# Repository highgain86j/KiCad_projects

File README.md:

# KiCad_projects
This repository contains works by the author using KiCad. May contain stuff that are very far from being complete...

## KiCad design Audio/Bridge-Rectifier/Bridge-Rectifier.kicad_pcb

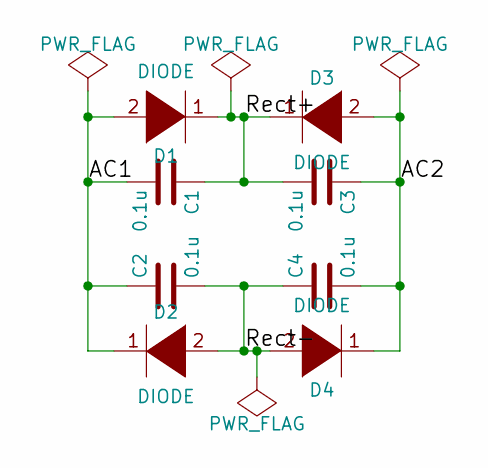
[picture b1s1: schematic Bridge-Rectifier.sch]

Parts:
C1, C2, C3, C4: 0.1u; C_Rect_L13_W6_H12_P10
D1, D2, D3, D4: DIODE; Diode_TO-220_Vertical

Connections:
/AC1: C1.2, C2.1, D1.2 (A), D2.1 (K)
/AC2: C3.1, C4.2, D3.2 (A), D4.1 (K)
/Rect+: C1.1, C3.2, D1.1 (K), D3.1 (K)
/Rect-: C2.2, C4.1, D2.2 (A), D4.2 (A)

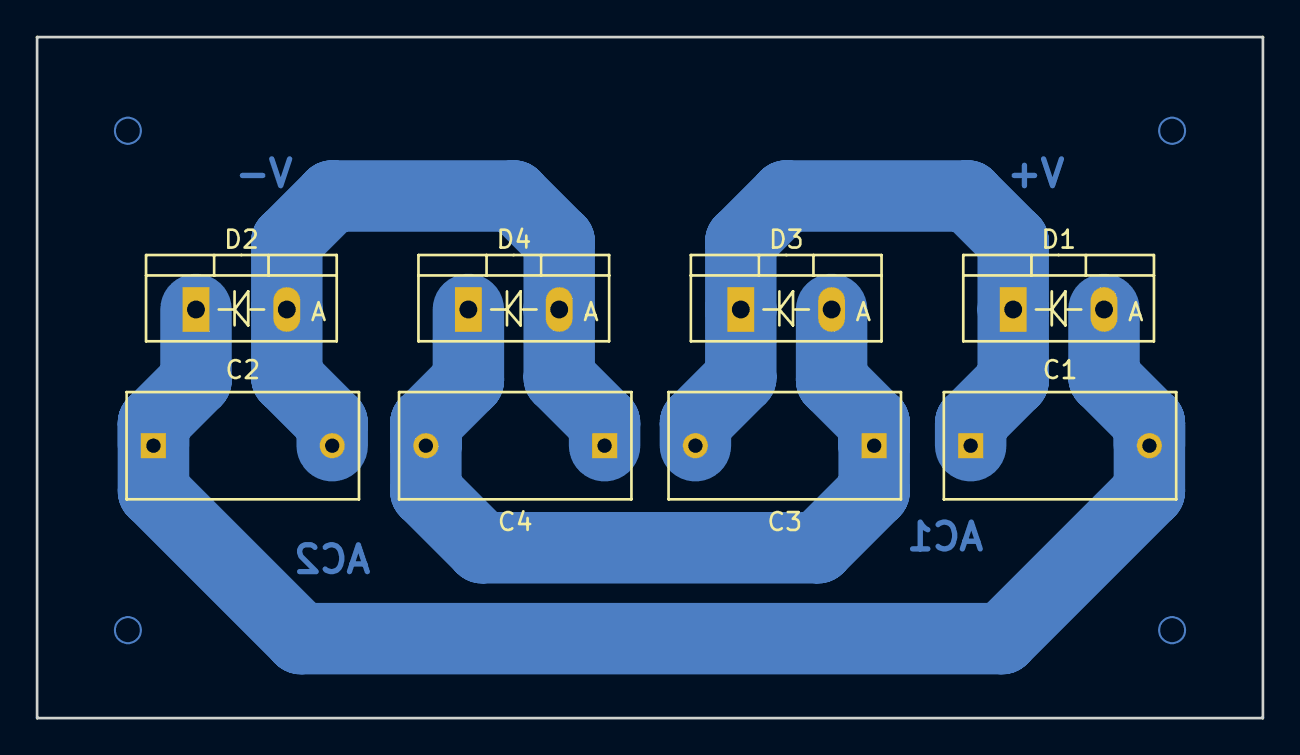
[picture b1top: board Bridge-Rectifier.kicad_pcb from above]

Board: 2 copper layers, 68.6 x 38.1 mm, 8 parts (0 on the bottom side), 4 nets.

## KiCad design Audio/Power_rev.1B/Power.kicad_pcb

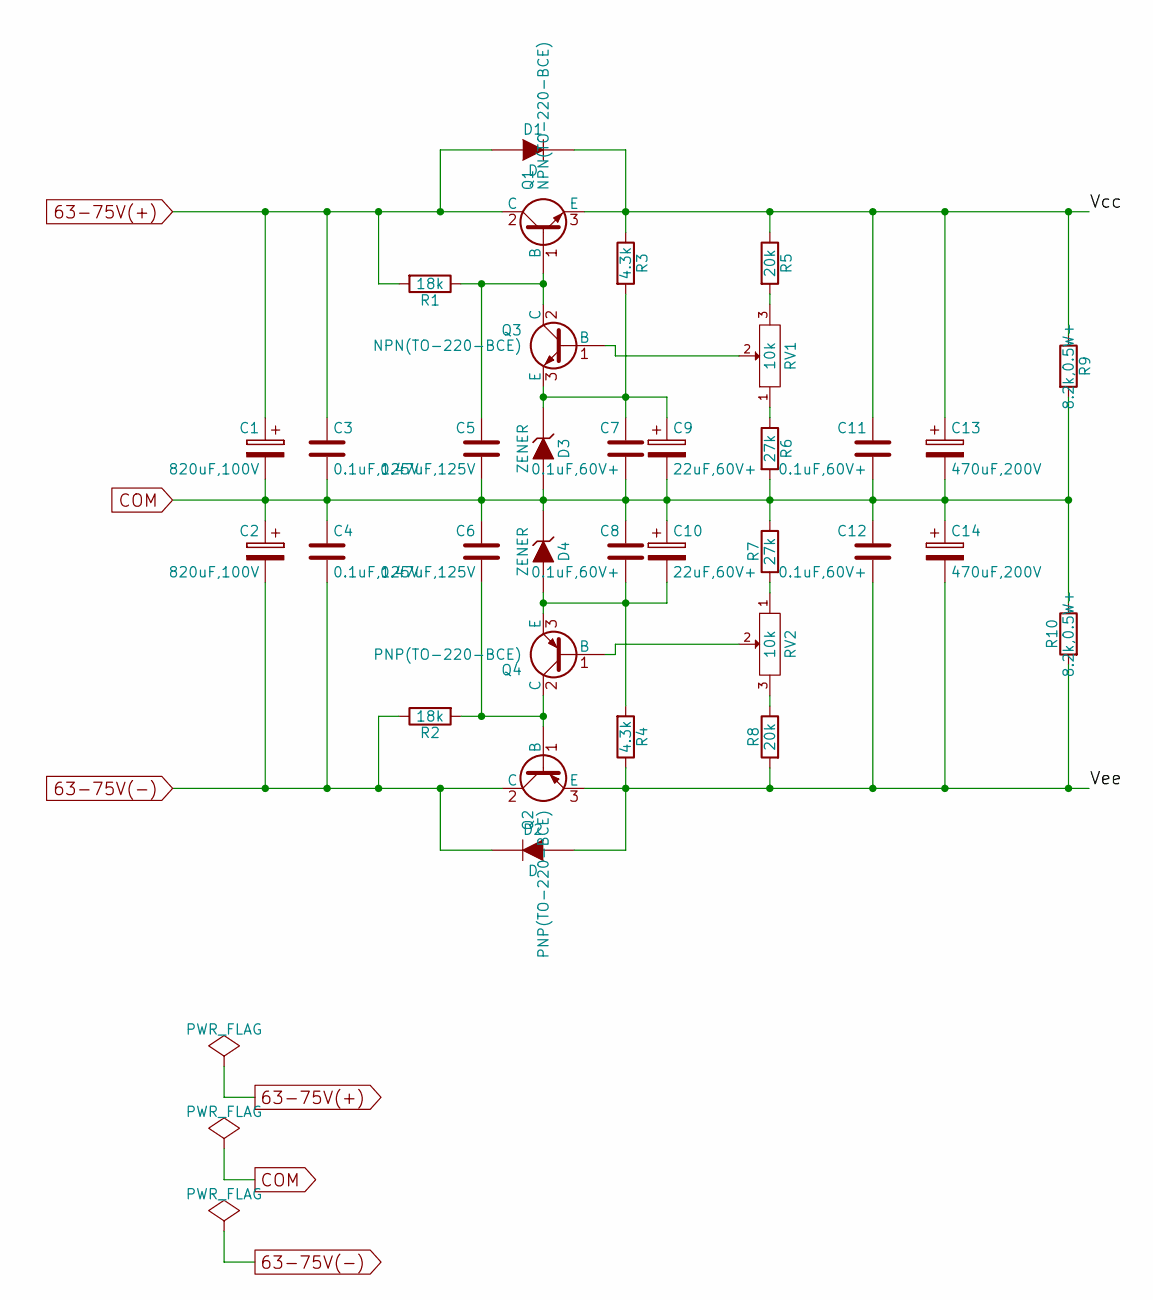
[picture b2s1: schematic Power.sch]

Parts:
C1, C2: 820uF,100V; C_Radial_D18_L36_P7.5
C3, C4: 0.1uF,125V; C_Rect_L18_W6_H12_P15
C5, C6: 0.47uF,125V; C_Rect_L18_W6_H12_P15
C7, C8, C11, C12: 0.1uF,60V+; C_Rect_L18_W6_H12_P15
C9, C10: 22uF,60V+; C_Radial_D10_L20_P5
C13, C14: 470uF,200V; C_Radial_D18_L36_P7.5
D1, D2: D; Diode_DO-35_SOD27_Horizontal_RM10
D3, D4: ZENER; Diode_DO-35_SOD27_Horizontal_RM10
Q1, Q3: NPN(TO-220-BCE); TO-220_Neutral123_Vertical_LargePads
Q2, Q4: PNP(TO-220-BCE); TO-220_Neutral123_Vertical_LargePads
R1, R2: 18k; Resistor_Horizontal_RM10mm
R3, R4: 4.3k; Resistor_Horizontal_RM10mm
R5, R8: 20k; Resistor_Horizontal_RM10mm
R6, R7: 27k; Resistor_Horizontal_RM10mm
R9, R10: 8.2k,0.5W+; Resistor_Horizontal_RM15mm
RV1, RV2: 10k; Potentiometer_Bourns_3296W_3-8Zoll_Inline_ScrewUp

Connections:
63-75V(+): C1.1, C3.1, D1.1 (A), Q1.2 (C), R1.2
63-75V(-): C2.2, C4.2, D2.2 (K), Q2.2 (C), R2.1
/Vcc: C11.1, C13.1, D1.2 (K), Q1.3 (E), R3.1, R5.1, R9.1
/Vee: C12.2, C14.2, D2.1 (A), Q2.3 (E), R4.1, R8.2, R10.2
COM: C1.2, C2.1, C3.2, C4.1, C5.2, C6.1, C7.2, C8.1, C9.2, C10.1, C11.2, C12.1, C13.2, C14.1, D3.2 (A), D4.1 (K), R6.2, R7.1, R9.2, R10.1
unnamed: C5.1, Q1.1 (B), Q3.2 (C), R1.1
unnamed: C6.2, Q2.1 (B), Q4.2 (C), R2.2
unnamed: C7.1, C9.1, D3.1 (K), Q3.3 (E), R3.2
unnamed: C8.2, C10.2, D4.2 (A), Q4.3 (E), R4.2
unnamed: Q3.1 (B), RV1.2
unnamed: Q4.1 (B), RV2.2
unnamed: R5.2, RV1.3
unnamed: R6.1, RV1.1
unnamed: R7.2, RV2.1
unnamed: R8.1, RV2.3

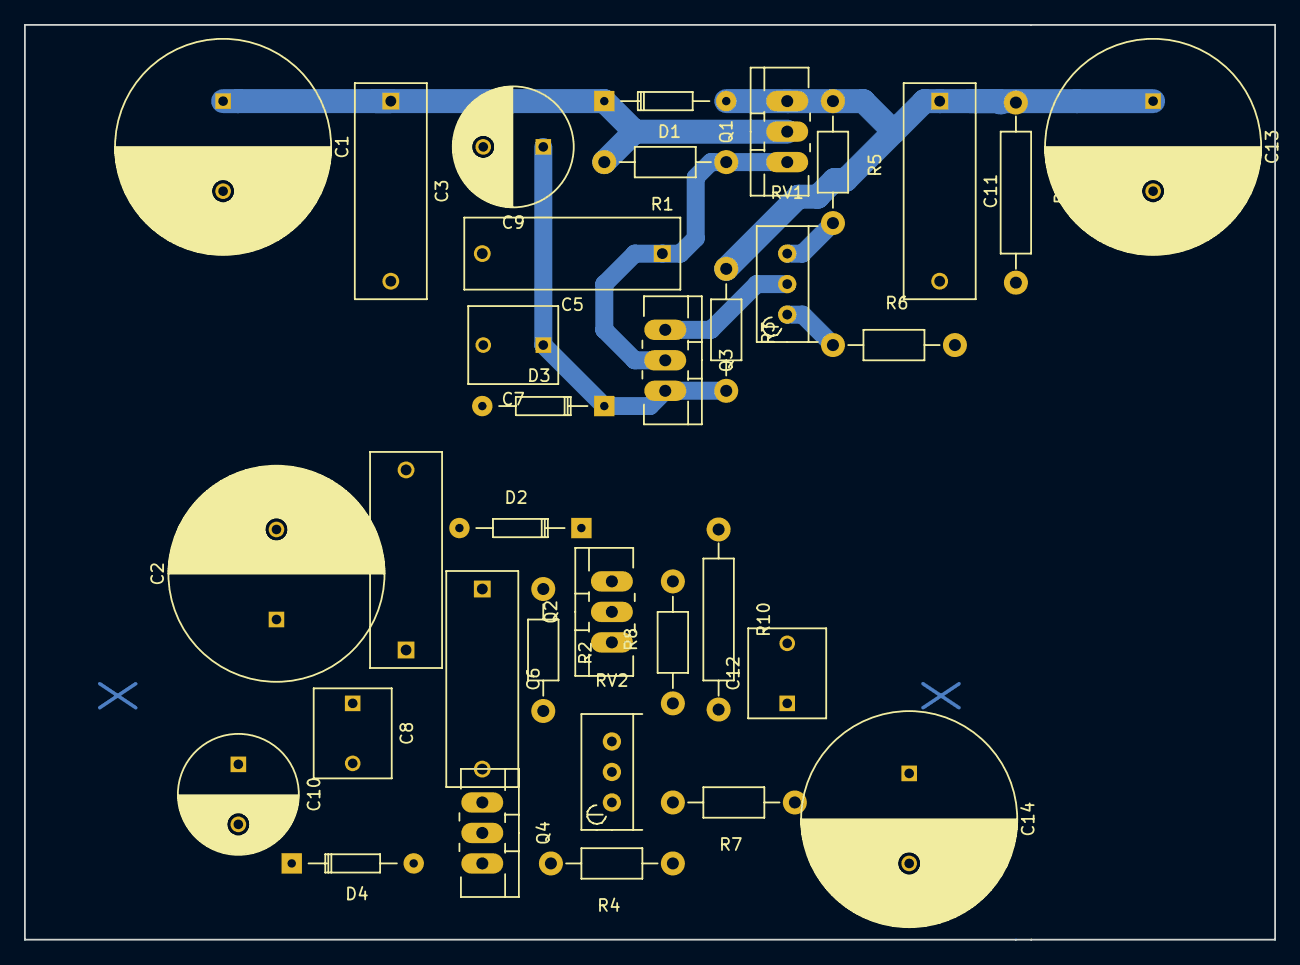
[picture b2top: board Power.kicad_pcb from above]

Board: 2 copper layers, 104.1 x 76.2 mm, 34 parts (0 on the bottom side), 15 nets.

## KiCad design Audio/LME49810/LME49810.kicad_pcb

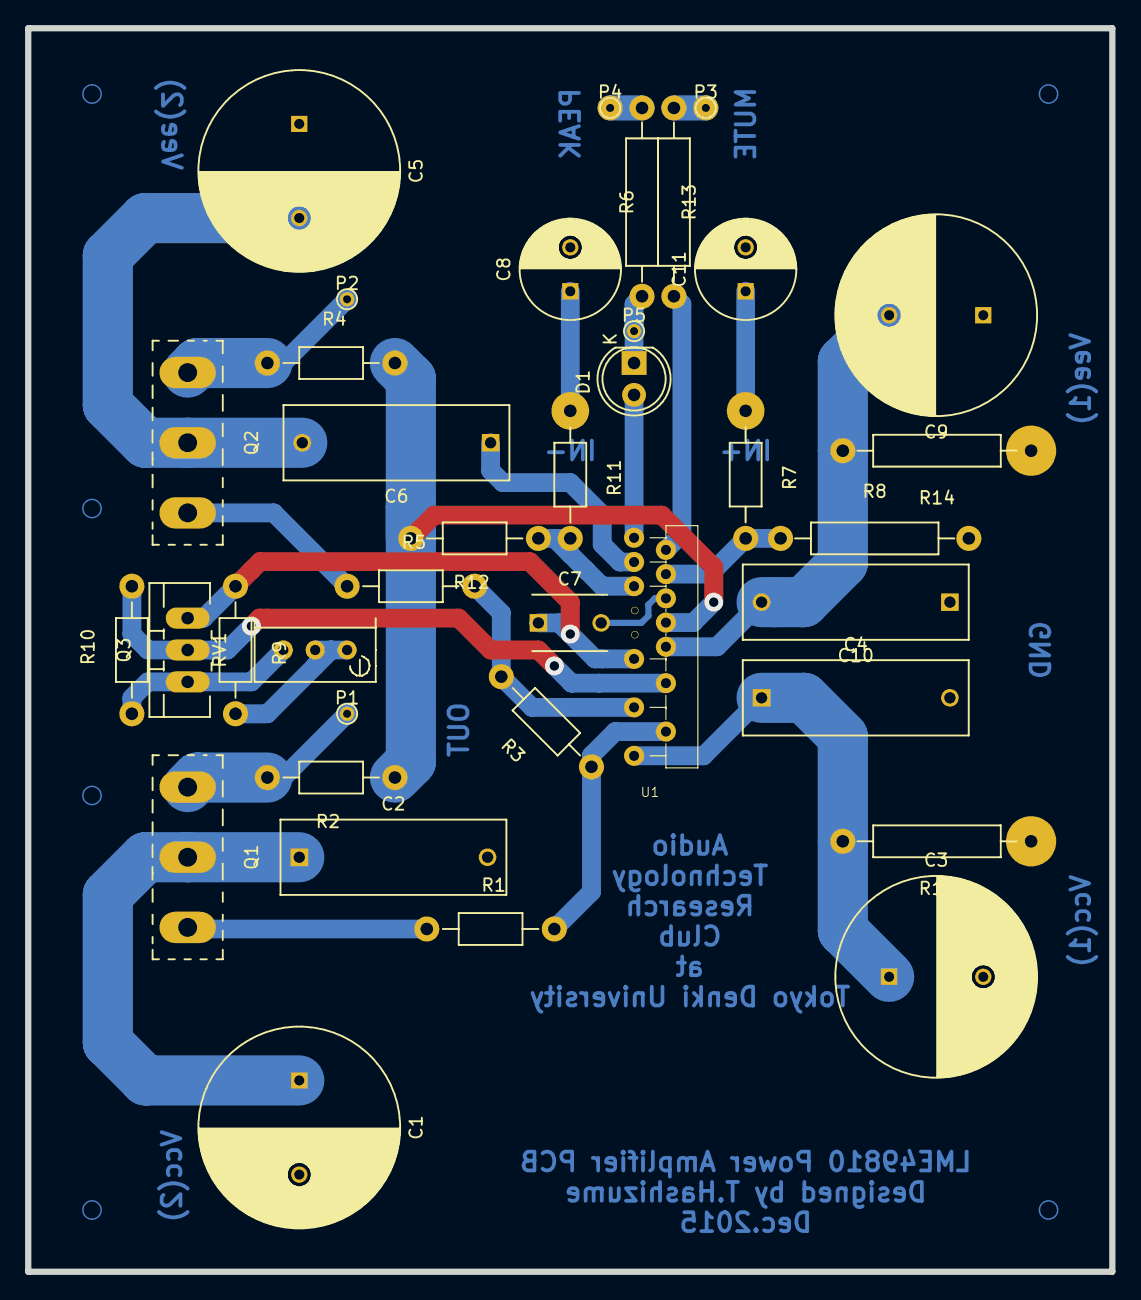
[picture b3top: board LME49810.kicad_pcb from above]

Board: 2 copper layers, 86.4 x 99.1 mm, 37 parts (0 on the bottom side), 26 nets.

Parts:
C1, C3, C5, C9: 820u,100V; C_Radial_D16_L31.5_P7.5
C2, C4, C6, C10: 0.1u; C_Rect_L18_W6_H12_P15
C7: 10p; C_Disc_D6_P5
C8: 220u; C_Radial_D8_L11.5_P3.5
C11: 470u; C_Radial_D8_L11.5_P3.5
D1: LED; LED-5MM
P1, P2, P3, P4, P5: CONN_01X01; PINTST
Q1: NPN(TO-3P-BCE); TO-247_Vertical_Neutral123_MountedFromLS
Q2: PNP(TO-3P-BCE); TO-247_Vertical_Neutral123_MountedFromLS
Q3: NPN(TO-220-BCE); TO-220_Neutral123_Vertical_LargePads
R1, R5: 100; Resistor_Horizontal_RM10mm
R2, R4: 0.22; Resistor_Horizontal_RM10mm
R3: 2.2k; Resistor_Horizontal_RM10mm
R6: 33k; Resistor_Horizontal_RM15mm
R7, R11: 470; Resistor_Horizontal_RM10mm
R8: 7.5k; Resistor_Horizontal_RM15mm
R9: 330; Resistor_Horizontal_RM10mm
R10: 1.2k; Resistor_Horizontal_RM10mm
R12: 7.5k; Resistor_Horizontal_RM10mm
R13: 470; Resistor_Horizontal_RM15mm
R14, R15: 10; Resistor_Horizontal_RM15mm
RV1: 500; Potentiometer_Bourns_3296W_3-8Zoll_Inline_ScrewUp
U1: LME49810

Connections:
+VccL2: C1.1, C2.1, Q1.2
-VeeL2: C5.2, C6.2, Q2.2
/Emit-NPN: P1.1, Q1.3, R2.2
/Emit-PNP: P2.1, Q2.3, R4.1
/IN+: C11.1, R7.1
/IN-: C8.1, R11.1
/Vcc: C3.1, C4.1, R15.2, U1.15
/Vee: C9.2, C10.2, R14.2, U1.10
BLH: Q3.1, R10.1, RV1.3
CLH: Q3.2, R10.2, U1.12
ELH: C7.1, Q3.3, R9.1, U1.11
GND1: C1.2, C2.2, C3.2, C4.2, C5.1, C6.1, C8.2, C9.1, C10.1, C11.2, R8.2, U1.3
unnamed: C7.2, U1.6
unnamed: D1.1, P5.1, R13.2
unnamed: D1.2, U1.1
unnamed: P3.1, R6.2
unnamed: P4.1, R13.1
unnamed: Q1.1, R1.1
unnamed: Q2.1, R5.1
unnamed: R6.1, U1.2
unnamed: R7.2, R8.1, U1.4
unnamed: R9.2, RV1.1, RV1.2
unnamed: R11.2, R12.1, U1.5
OUTLH: R2.1, R4.2, R12.2, U1.8
SinkLH: R3.2, R5.2, U1.13
SourceLH: R1.2, R3.1, U1.14

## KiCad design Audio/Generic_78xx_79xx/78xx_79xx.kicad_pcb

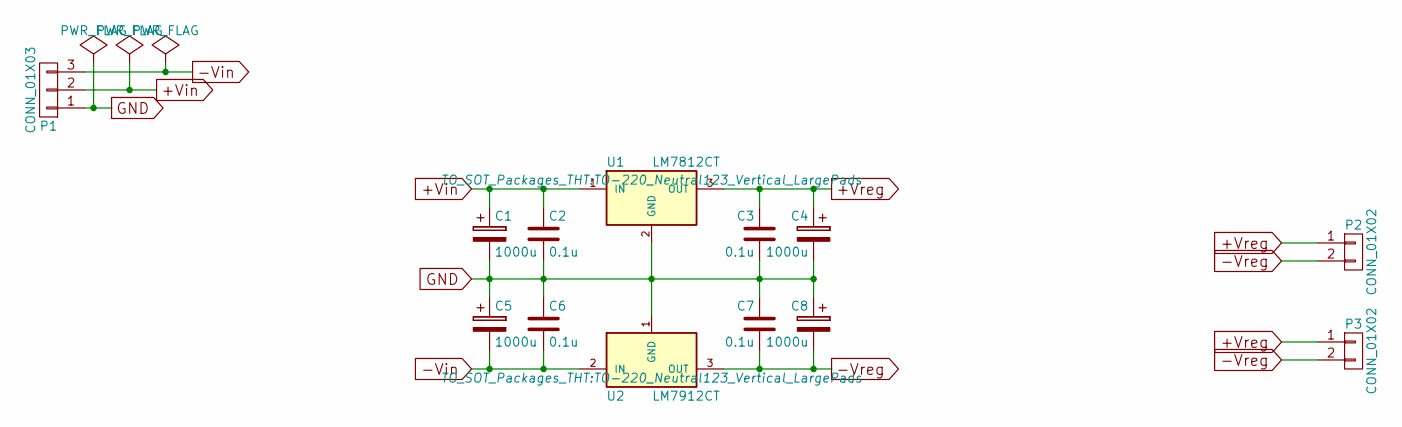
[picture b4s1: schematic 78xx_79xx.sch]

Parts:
C1, C4, C5, C8: 1000u; C_Radial_D16_L25_P7.5
C2, C3, C6, C7: 0.1u; C_Disc_D6_P5
P1: CONN_01X03; PINHEAD1-3
P2, P3: CONN_01X02; PINHEAD1-2
U1: LM7812CT; TO-220_Neutral123_Vertical_LargePads
U2: LM7912CT; TO-220_Neutral123_Vertical_LargePads

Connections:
+Vin: C1.1, C2.1, P1.2, U1.1 (IN)
+Vreg: C3.1, C4.1, P2.1, P3.1, U1.3 (OUT)
-Vin: C5.2, C6.2, P1.3, U2.2 (IN)
-Vreg: C7.2, C8.2, P2.2, P3.2, U2.3 (OUT)
GND: C1.2, C2.2, C3.2, C4.2, C5.1, C6.1, C7.1, C8.1, P1.1, U1.2 (GND), U2.1 (GND)

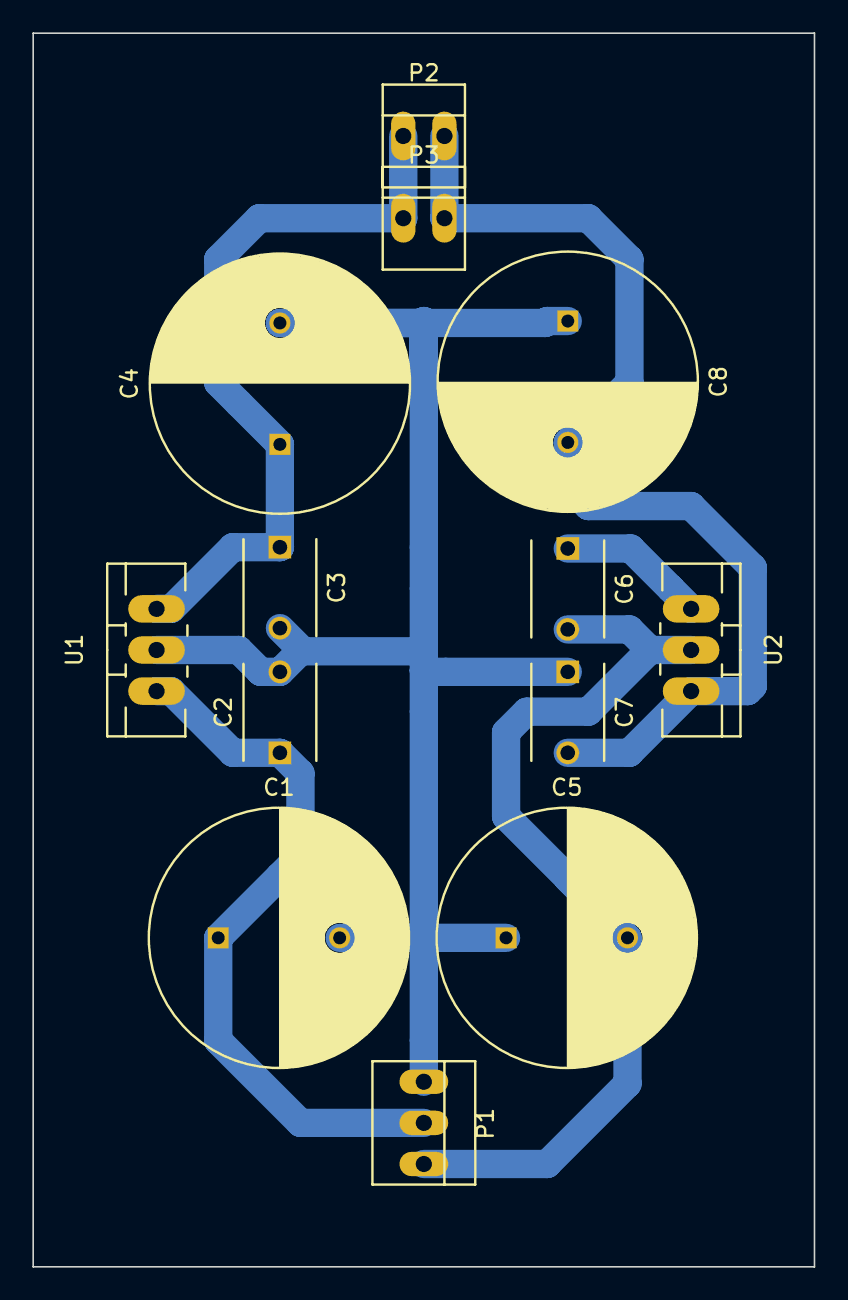
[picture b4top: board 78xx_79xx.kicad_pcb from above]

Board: 2 copper layers, 48.3 x 76.2 mm, 13 parts (0 on the bottom side), 5 nets.

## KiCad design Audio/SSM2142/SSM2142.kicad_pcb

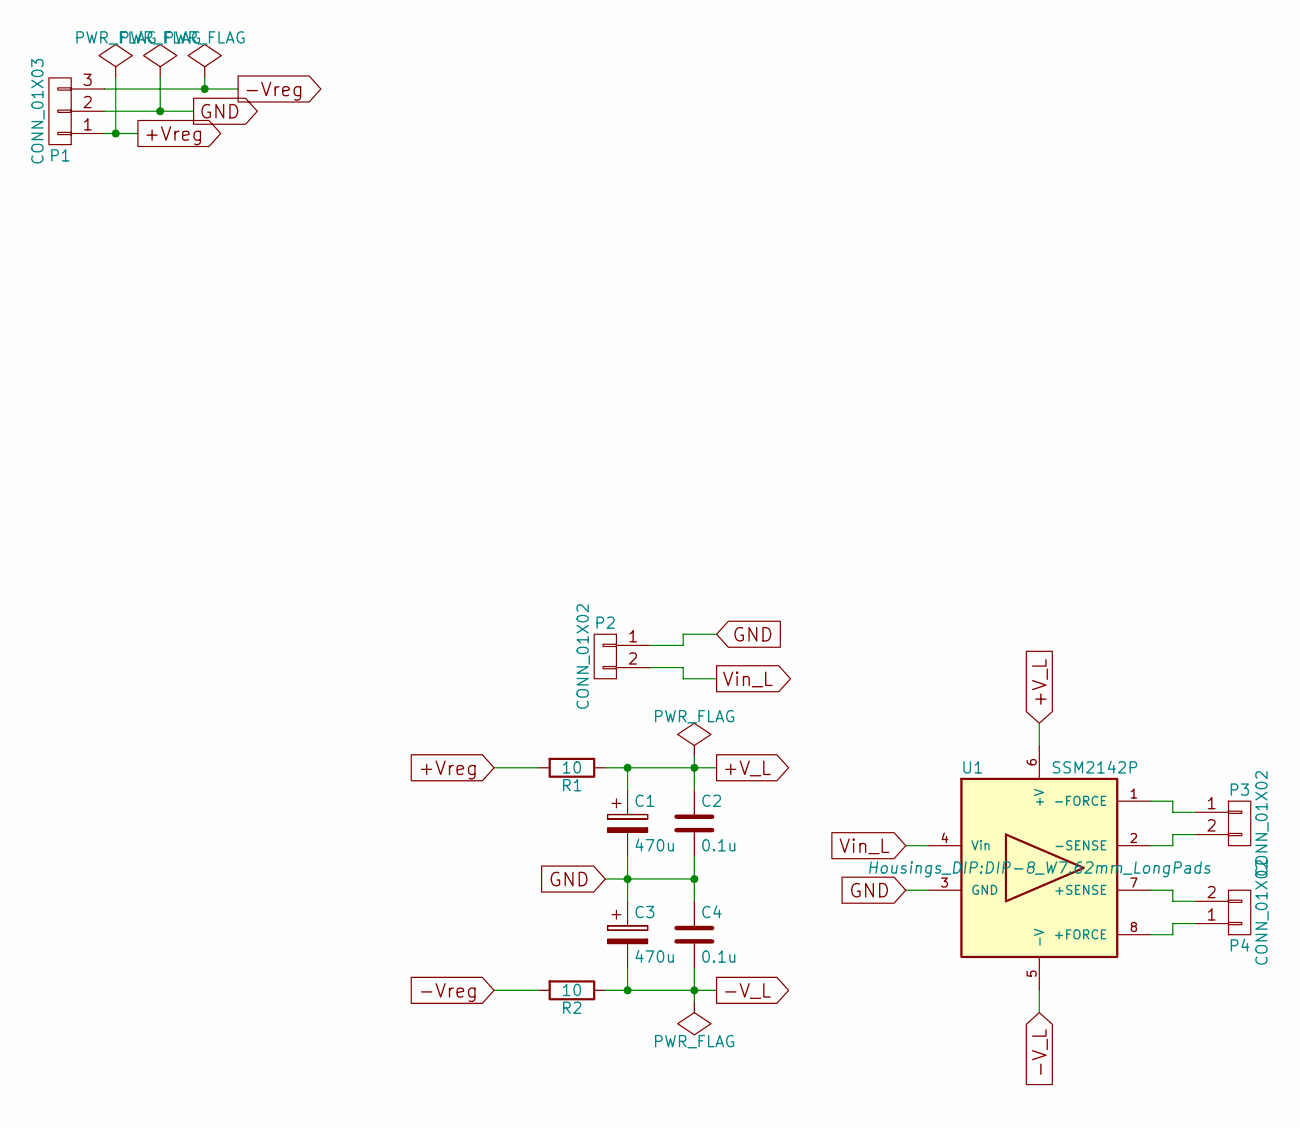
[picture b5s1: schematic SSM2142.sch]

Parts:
C1, C3: 470u; C_Radial_D16_L25_P7.5
C2, C4: 0.1u; C_Disc_D6_P5
P1: CONN_01X03; PINHEAD1-3
P2, P3, P4: CONN_01X02; PINHEAD1-2
R1, R2: 10; Resistor_Horizontal_RM10mm
U1: SSM2142P; DIP-8_W7.62mm_LongPads

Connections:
+V_L: C1.1, C2.1, R1.1, U1.6 (+V)
+Vreg: P1.1, R1.2
-V_L: C3.2, C4.2, R2.1, U1.5 (-V)
-Vreg: P1.3, R2.2
GND: C1.2, C2.2, C3.1, C4.1, P1.2, P2.1, U1.3 (GND)
unnamed: P3.1, U1.1 (-FORCE)
unnamed: P3.2, U1.2 (-SENSE)
unnamed: P4.1, U1.8 (+FORCE)
unnamed: P4.2, U1.7 (+SENSE)
Vin_L: P2.2, U1.4 (Vin)

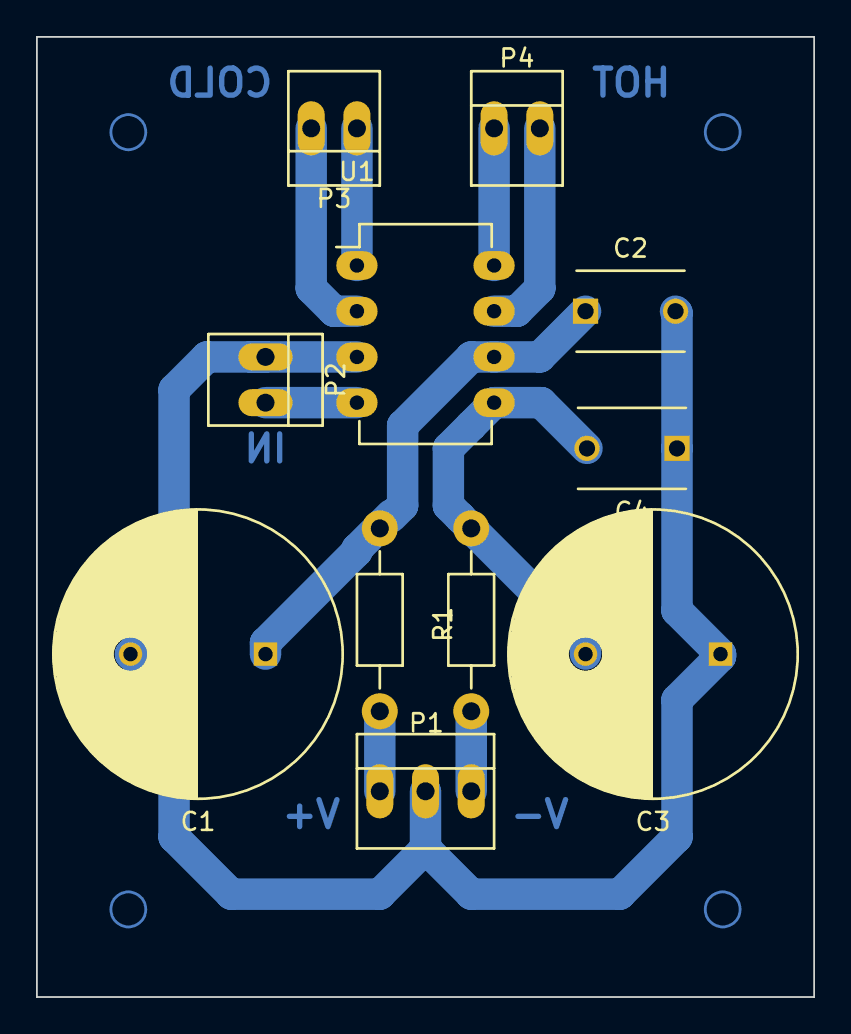
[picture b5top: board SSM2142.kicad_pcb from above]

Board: 2 copper layers, 43.2 x 53.3 mm, 11 parts (0 on the bottom side), 10 nets.

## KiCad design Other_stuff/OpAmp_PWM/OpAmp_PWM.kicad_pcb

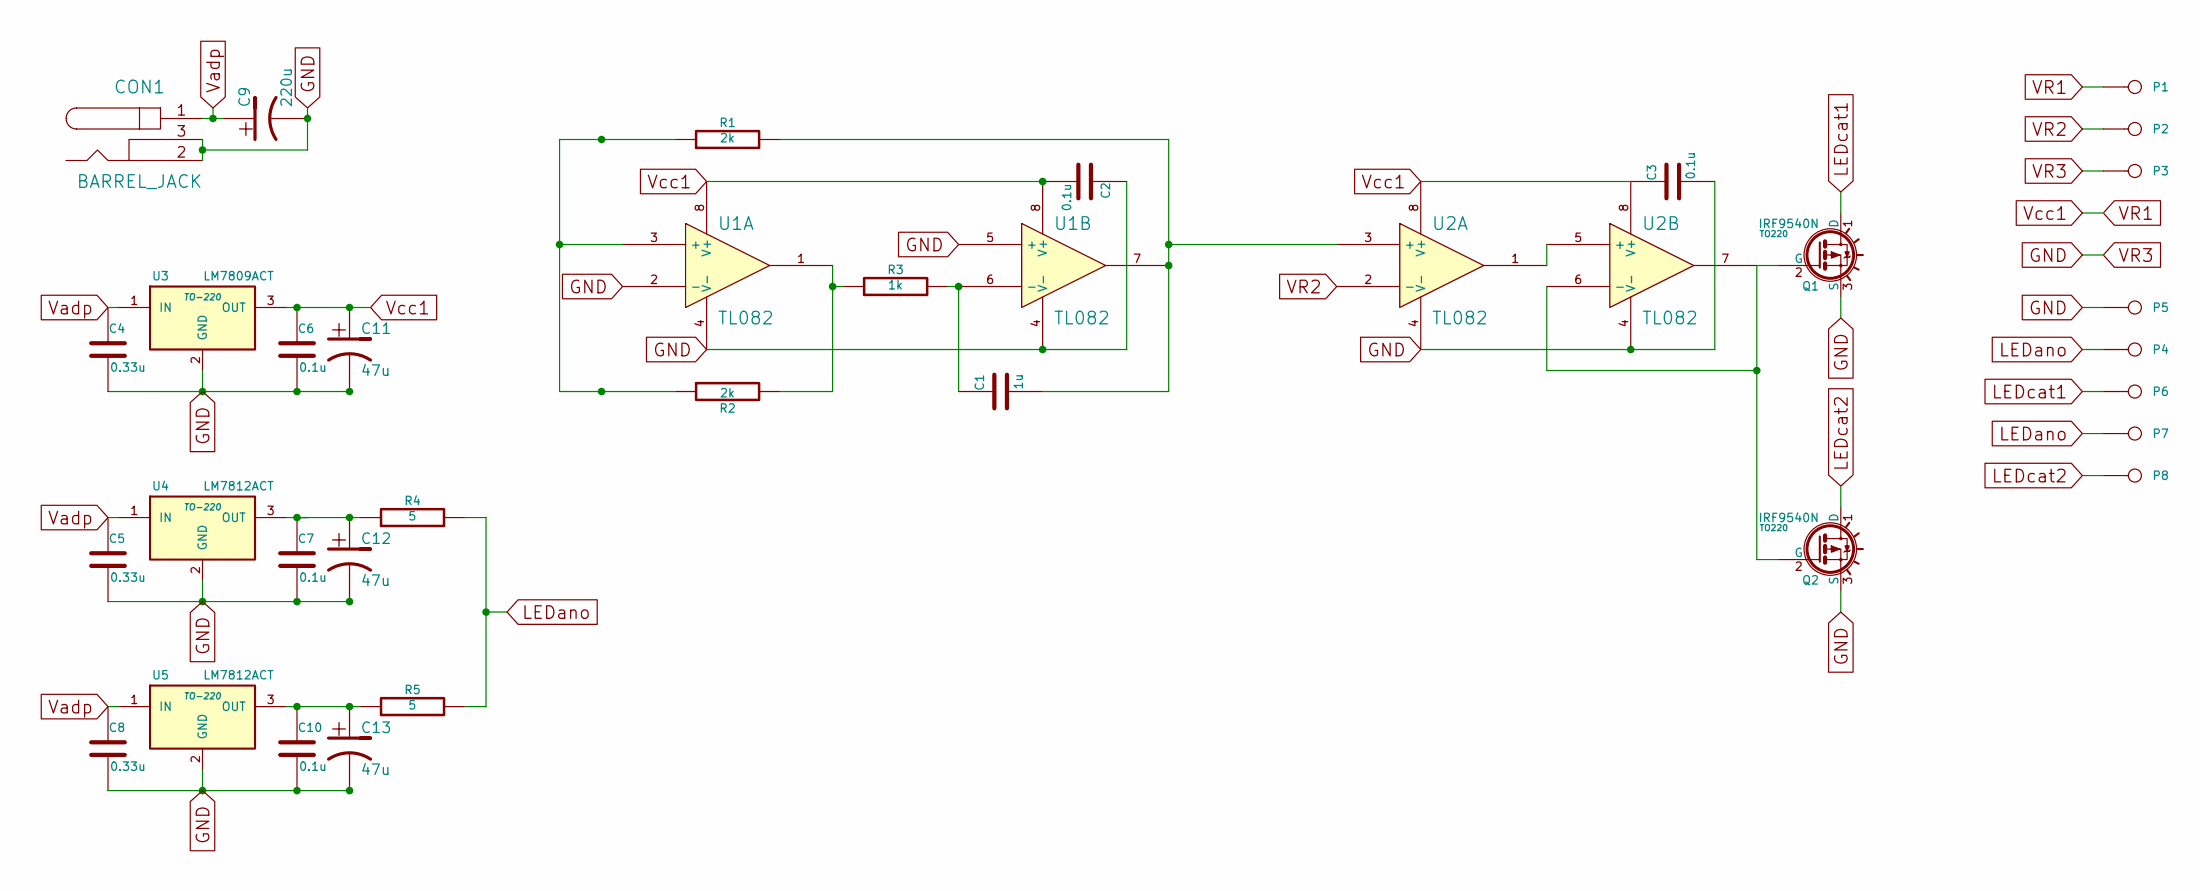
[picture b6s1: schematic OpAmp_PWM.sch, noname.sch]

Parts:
C1: 1u
C2, C3, C6, C7, C10: 0.1u
C4, C5, C8: 0.33u
C9: 220u
C11, C12, C13: 47u
CON1: BARREL_JACK
P1, P2, P3, P4, P5, P6, P7, P8: CONN_1
Q1, Q2: IRF9540N; TO220
R1, R2: 2k
R3: 1k
R4, R5: 5
U1, U2: TL082
U3: LM7809ACT; TO-220
U4, U5: LM7812ACT; TO-220

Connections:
GND: C2.1, C3.2, C4.2, C5.2, C6.2, C7.2, C8.2, C9.2, C10.2, C11.2, C12.2, C13.2, CON1.2, CON1.3, P3.1, P5.1, Q1.3 (S), Q2.3 (S), U1.2 (-), U1.4 (V-), U1.5 (+), U2.4 (V-), U3.2 (GND), U4.2 (GND), U5.2 (GND)
LEDano: P4.1, P7.1, R4.2, R5.2
LEDcat1: P6.1, Q1.1 (D)
LEDcat2: P8.1, Q2.1 (D)
unnamed: C10.1, C13.1, R5.1, U5.3 (OUT)
unnamed: C7.1, C12.1, R4.1, U4.3 (OUT)
unnamed: Q1.2 (G), Q2.2 (G), U2.6 (-), U2.7
unnamed: U2.1, U2.5 (+)
unnamed: C1.2, R1.2, U1.7, U2.3 (+)
unnamed: R2.2, R3.1, U1.1
unnamed: C1.1, R3.2, U1.6 (-)
unnamed: R1.1, R2.1, U1.3 (+)
VR1: C2.2, C3.1, C6.1, C11.1, P1.1, U1.8 (V+), U2.8 (V+), U3.3 (OUT)
VR2: P2.1, U2.2 (-)
Vadp: C4.1, C5.1, C8.1, C9.1, CON1.1, U3.1 (IN), U4.1 (IN), U5.1 (IN)

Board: 2 copper layers, 34 parts (0 on the bottom side), 15 nets, no tracks yet.

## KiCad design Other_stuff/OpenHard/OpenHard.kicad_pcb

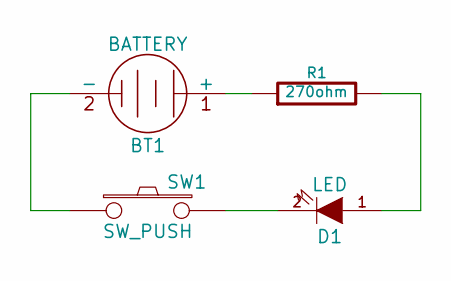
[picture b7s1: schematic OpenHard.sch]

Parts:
BT1: BATTERY
D1: LED
R1: 270ohm
SW1: SW_PUSH

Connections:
unnamed: D1.1 (A), R1.2
unnamed: BT1.1 (+), R1.1
unnamed: BT1.2 (-), SW1.1
unnamed: D1.2 (K), SW1.2

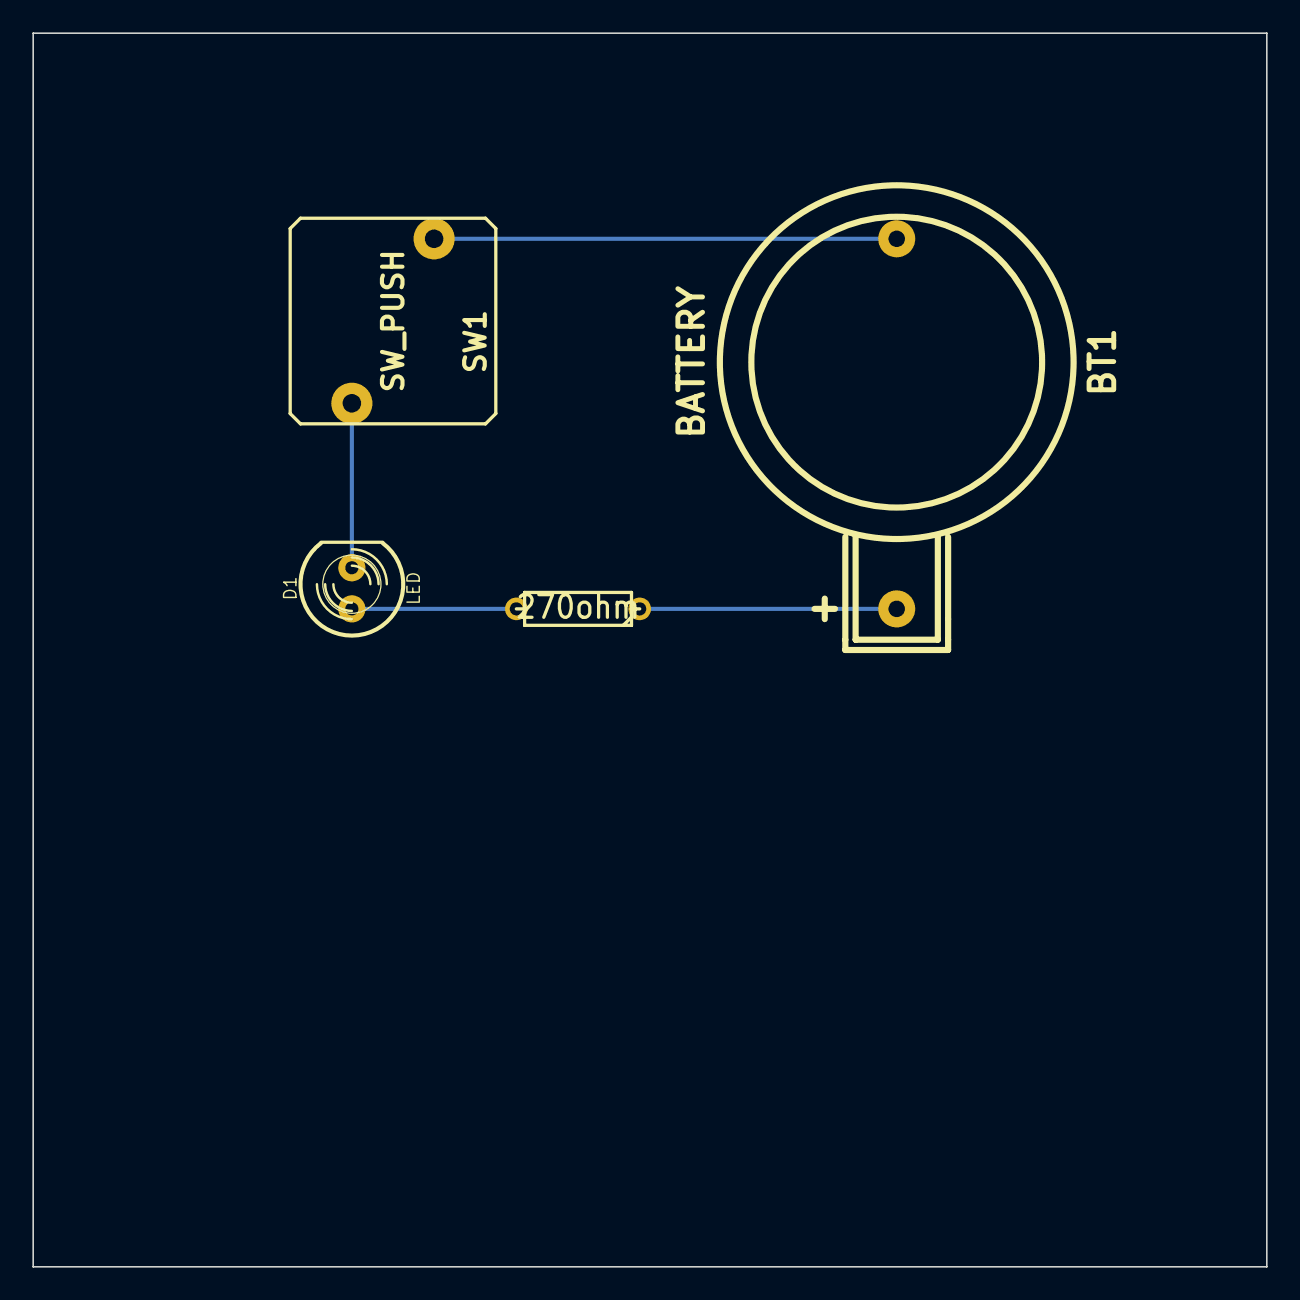
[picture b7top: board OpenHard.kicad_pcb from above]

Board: 2 copper layers, 76.2 x 76.2 mm, 4 parts (0 on the bottom side), 4 nets.

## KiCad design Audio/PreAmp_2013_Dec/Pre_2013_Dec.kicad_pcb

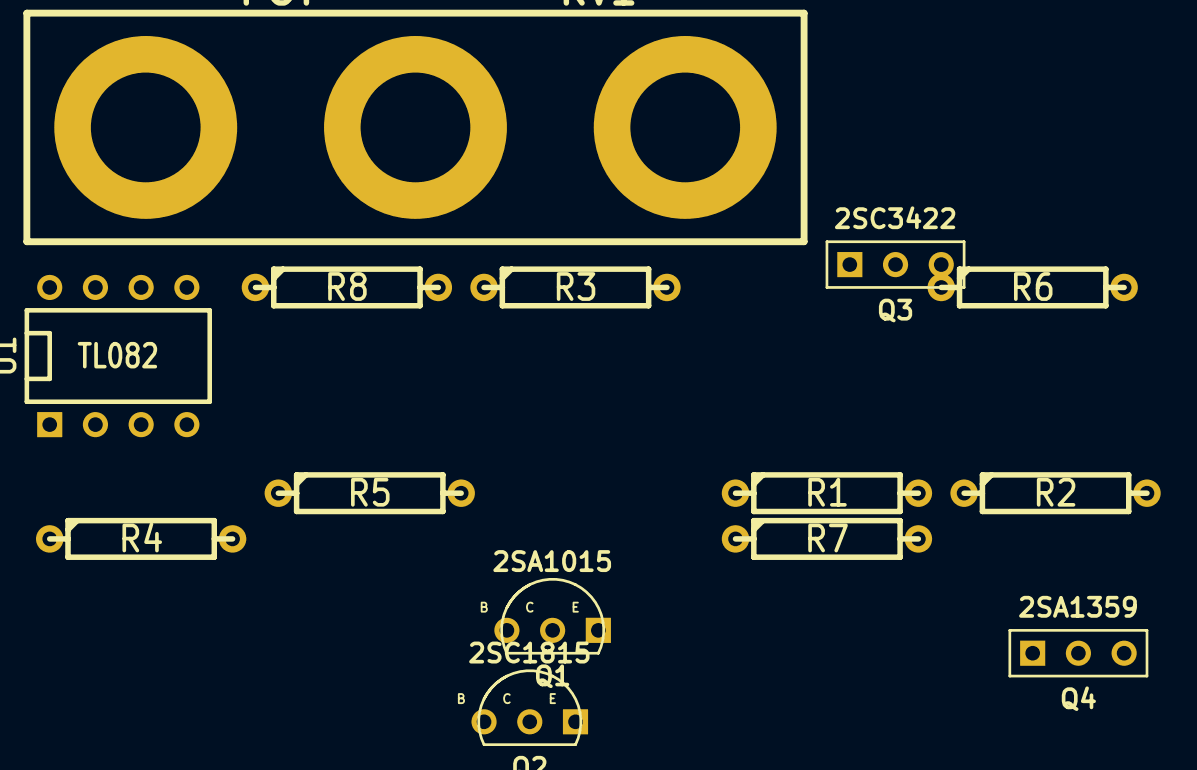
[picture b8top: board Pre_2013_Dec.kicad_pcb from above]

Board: 2 copper layers, 14 parts (0 on the bottom side), 11 nets, no tracks yet.

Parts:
Q1: 2SA1015; TO92-ECB
Q2: 2SC1815; TO92-ECB
Q3: 2SC3422; TO126-ECB
Q4: 2SA1359; TO126-ECB
R1, R2, R3, R4, R5, R6, R7, R8: R; R4
RV1: POT; 3PIN_6mm
U1: TL082; DIP-8__300

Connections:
BUF1_OUT: R5.2, R6.1, R7.1
BUF1_V+: Q2.2, R3.1
BUF1_V-: Q1.2, R4.2
GND: R1.1, R8.2, RV1.3
unnamed: R7.2, R8.1
unnamed: Q2.1, R4.1
unnamed: Q1.1, R3.2
unnamed: RV1.2, U1.3
unnamed: Q1.3, Q2.3, R2.2
unnamed: R1.2, R2.1, U1.1
OPA_V+: U1.4, U1.8

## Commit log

2015-12-09 Added a project
    Added PHILIPS_DAC7 for designs with TDA1547
2015-12-09 Added a project
    Added the modification project for DENON AVC-S511HD.
2015-12-09 Added a project
    Electronic attenuator with PGA2311
2015-12-09 Added a project
    SSM2142 differential line driver PCB
2015-12-09 Added a project
    Power Amplifier with LME49810
2015-12-09 Added a project
    ADC with TI's PCM1804
2015-12-09 Added two projects dealing with linear regulators
    Power_rev.1A is based on 78xx with Zenar.
    Power_rev.1B is designed in descrete.
2015-12-09 Added a project
    PreAmp_2013 is as it reads. Massive work to be done.
2015-12-09 Added a project
    Experimenting with the "Diamond Buffer"
2015-12-09 Added a project
    My dream...
2015-12-09 Added a project
    Very handy "dual supply" PCB for amplifier builders.
2015-12-09 Added a project
    This was a teaching material for the KiCad lecture on 5th Oct. 2014 at
    Geek-house Kanda.
2015-12-09 Added a project
    Brush-less DC motor controller...
2015-12-09 Added a project
    Primitive PWM with OpAmps
2015-12-09 Clean-up.
    Removed ".dropbox.attr" files
2015-12-10 Fix
    Fixed for ERC cpmpliance.
2015-12-10 further tweaking(1)
2015-12-11 Further revision
    More fixes
2015-12-11 Improvements
    PCB revised.
2015-12-11 Fixes for SSM2142(PCB)
    Reworked for smaller footprint of PCB.
2015-12-12 BOM added for LME49810
2015-12-13 Fixes
    More fixes done
2015-12-14 Fixes on component conflict
    LME49810 PCB revised
